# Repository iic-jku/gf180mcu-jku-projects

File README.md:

# wafer.space gf180mcuD MPW Multi-Project Chip

(c) 2025-2026 Simon Dorrer (JKU), Jonathan Hager (JMU), Dominik Brandstetter (JKU) and [co-designers](https://github.com/iic-jku/gf180mcu-jku-projects/blob/main/AUTHORS.md).

Project `JKU1` for wafer.space MPW run using the `gf180mcuD` PDK.

<p align="center">
  
  <br>
  <em>Chip-on-Board (CoB) wire-bonded die of the wafer.space gf180mcuD chip.</em>
</p>

<p align="center">
  
  <br>
  <em>Micrograph of CoB wire-bonded die of the wafer.space gf180mcuD chip with ruler on the right side.</em>
</p>

<p align="center">
  
  &nbsp;
  
  <br>
  <em>Micrograph of the bare die (left) and render of the layout (right) of the wafer.space gf180mcuD chip (4mm x 5mm).</em>
</p>

## Sanity Bring-Up Test

We wired up the DIP adapter PCB on a breadboard. We supplied the board with 3V3 or 5V via decoupling capacitors, connected an AWG to the clock input, and tied the reset input to high: the sanity bring-up test works. On one digital output, the Super Mario Bros. theme song is played via a buzzer through a PWM signal. Nothing fancy, just a quick breadboard build-up and test, but at least we can say that the chip is alive!

https://github.com/user-attachments/assets/dcc359f1-c54c-4383-b16b-32720ad51963
<p align="center">
  <em>Sanity bring-up test playing the Super Mario Bros. theme song.</em>
</p>

## Overview

- [x] **GDS Submission:** https://platform.wafer.space/
- [x] **Precheck:** https://github.com/wafer-space/gf180mcu-precheck
- [x] **Projects (Pass):**
  - [x] Multiplexer (Simon Dorrer - JKU)
    - **N/A Reg to Reg Paths**
  - [x] TinyWhisper RISC-V (Jonathan Hager - JMU)
    - **setup violation for SS corner**
  - [x] TinyTone (Jakob Schaumberger - JKU)
  - [x] Decimation Filter (Michael Köfinger - JKU)
    - **N/A Reg to Reg Paths**
  - [x] Octowave (Max Golser - JKU)
    - **setup violation for SS corner**
  - [x] Tetris (Dominik Brandstetter - JKU & HTL Leonding)
    - **setup violation for SS corner**
  - [x] TinyStack (Linzer Technikum)
  - [x] TinyBF (Rene Hahn - JKU)
  - [x] SAR ADC Controller (Ilir Shala - JKU)
  - [x] LED Spinner (Tim Tremetsberger - JKU)
    - **N/A Reg to Reg Paths**
  - [x] TinyToneGen (Felix Feierabend - JKU)
    - **N/A Reg to Reg Paths**
  - [x] Digital Filter (Gregor Flachs - JKU)
  - [x] Traffic Light Controller (Maximilian Kernmaier - JKU)
  - [x] VGA Clock (Timo Laimer - JKU)
    - **setup violation for SS corner**

## Prerequisites

We use a custom fork of the [gf180mcuD PDK variant](https://github.com/wafer-space/gf180mcu) until all changes have been upstreamed.

To clone the latest PDK version, simply run `make clone-pdk`.

In the next step, use LibreLane within the IIC-OSIC-TOOLS container with tag `2026.04` or later or install LibreLane by following the Nix-based installation instructions: https://librelane.readthedocs.io/en/latest/installation/nix_installation/index.html

## Implement the Design

This repository contains a Nix flake that provides a shell with the [`leo/gf180mcu`](https://github.com/librelane/librelane/tree/leo/gf180mcu) branch of LibreLane.

Simply run `nix-shell` in the root of this repository.

> [!NOTE]
> Since we are working on a branch of LibreLane, OpenROAD needs to be compiled locally. This will be done automatically by Nix, and the binary will be cached locally. 

With this shell enabled, run the implementation:

```
make librelane
```

This command is also available for the macros.

## View the Design

After completion, you can view the design using the OpenROAD GUI:

```
make librelane-openroad
```

Or using KLayout:

```
make librelane-klayout
```

These commands are also available for the macros.

## Copying important Reports to the Reports Folder

To copy yosys, antenna violations, hold & setup timing and manufacturability reports of the latest run to the `reports/` folder in the root directory of the repository, run the following command:

```
make copy-reports
```

This will only work if the last run was completed without errors. This command is also available for the macros.

## Copying the Design to the Final Folder

To copy your latest run to the `final/` folder in the root directory of the repository, run the following command:

```
make copy-final
```

This will only work if the last run was completed without errors. This command is also available for the macros.

## Copying the final GDS to the GDS Folder

To copy and ZIP your latest GDS in the `final/` folder in the root directory of the repository and save it in the `gds/` folder, run the following command:

```
make copy-gds
```

This will only work if the last run was completed without errors.

## Render Layout of the Design

To render your latest GDS in the `final/` folder in the root directory of the repository and save it in the `img/` folder, run the following command:

```
make render-image
```

This will only work if the last run was completed without errors. This command is also available for the macros.

## Build Macros

To build a specific macro, look into the `Makefile` and run the corresponding command. For example, the following command builds the `tetris` macro:

```
make build-tetris
```

To build all macros, run the following command:

```
make build-all-macros
```

For each macro the following commands are executed: `make librelane`, `make copy-reports`, `make copy-final` and `make render-image`.

## Build All

To clone the PDK, build all macros, build the top-level chip, copy its reports, copy its `final/` folder, copy and ZIP its GDS, render its GDS and display it in the OpenROAD GUI, run the following command:

```
make build-all
```

This is especially useful for people who want to rebuild our chip from scratch. Just clone this repo, run `nix-shell` in the root of this repository and run `make build-all`. Enjoy. :-)

## Verification and Simulation

We use [cocotb](https://www.cocotb.org/), a Python-based testbench environment, for the verification of the chip.
The underlying simulator is Icarus Verilog (https://github.com/steveicarus/iverilog).

The testbench is located in `cocotb/chip_top_tb.py`. To run the RTL simulation, run the following command:

```
make sim
```

To run the GL (gate-level) simulation, run the following command:

```
make sim-gl
```

> [!NOTE]
> You need to have the latest implementation of your design in the `final/` folder. After implementing the design, execute 'make copy-final' to copy all necessary files.

In both cases, a waveform file will be generated under `cocotb/sim_build/chip_top.fst`.
You can view it using a waveform viewer, for example, [GTKWave](https://gtkwave.github.io/gtkwave/).

```
make sim-view
```

You can now update the testbench according to your design.

## Cite This Work

```
@software{2025_WS_MPW,
	author = {Dorrer, Simon and Hager, Jonathan},
	month = dec,
	year = {2025},
	title = {{GitHub Repository for a wafer.space MPW Multi-Project Chip}},
	url = {https://github.com/iic-jku/gf180mcu-jku-projects},
	doi = {10.5281/zenodo.19654471}
}
```

## Acknowledgements

This project is supported by [wafer.space](https://wafer.space/) and the [Johannes Kepler University](https://jku.at).

<table width="100%">
  <tr>
    <td align="left" width="50%">
      
    </td>
    <td align="right" width="50%">
      
    </td>
  </tr>
</table>

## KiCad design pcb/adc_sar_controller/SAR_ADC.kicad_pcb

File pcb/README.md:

# PCB Notes

## Authors

- Simon Dorrer
- Dominik Brandstetter
- Jakob Schaumberger
- Max Zaglmayr
- Max Golser
- Rene Hahn

## TODO

- Order DIP breakout boards: Simon Dorrer

## Links

- CoB breakout board: https://github.com/wafer-space/chip-on-board-wire-bonded-pcbs
- Tiny Tapeout demo PCB: https://github.com/TinyTapeout/tt-demo-pcb
- Tiny Tapeout PCB files: https://github.com/TinyTapeout/pcb-files
- Tiny Tapeout GF 0p2 mezzanine adapter PCB: https://github.com/htfab/breakout-ttgf0p2-ws-adapter
- VGA breakout board: https://github.com/mole99/tiny-vga
- GF180MCU-D JKU projects: https://github.com/iic-jku/gf180mcu-jku-projects

## Required Components

### General

- 1x 3-bit DIP switch
- 3x buttons + reset
- Copy the Tiny Tapeout VGA breakout board
- External GPIO headers (see Tiny Tapeout demo PCB)
- Fan for cooling (optional)

### MCU

- See Tiny Tapeout demo PCB
- Connect all inputs to the MCU
- Connect all outputs to the MCU
- USB-C
- I2C display
- Pin count TBD: PCA9555 IO/I2C or RP2350
- Level shifter (3.3 V / 5 V)

### Octowave

- Multiple-feedback filters (Max Golser)

### TinyWhisper

- See TinyWhisper PCB (Simon Dorrer)

### Decimation Filter

- SPI

### TinyTone

- Switching transistor + buzzer

### Tetris

- SNES connector to MCU (copy from Tiny Tapeout demo PCB)
- VGA output (see Tiny Tapeout demo PCB)
- Dominik Brandstetter + HTL Leonding

### TinyStack

- 8x LEDs

### TinyBF

- Input + Outputs to MCU
- UART + Testpads

### SAR ADC Controller

- Do not connect `comp_in` with MCU
- Connect 8-Bit DAC traces with MCU and DAC (switchable)
- Analog Front-End (maybe provided by Ilir)
	- DAC
	- Comparator
	- S&H

### LED Spinner

- 7-segment display (see Tiny Tapeout boards)
- Buttons

### TinyToneGen

- Low-pass active filter

### Digital Filter

- MCU only

### Traffic Light Control

- LED matrix for pedestrian signs
- LEDs for traffic lights
- Silkscreen for pedestrian crossing

### VGA Clock

- Combine VGA with Tetris (OR)

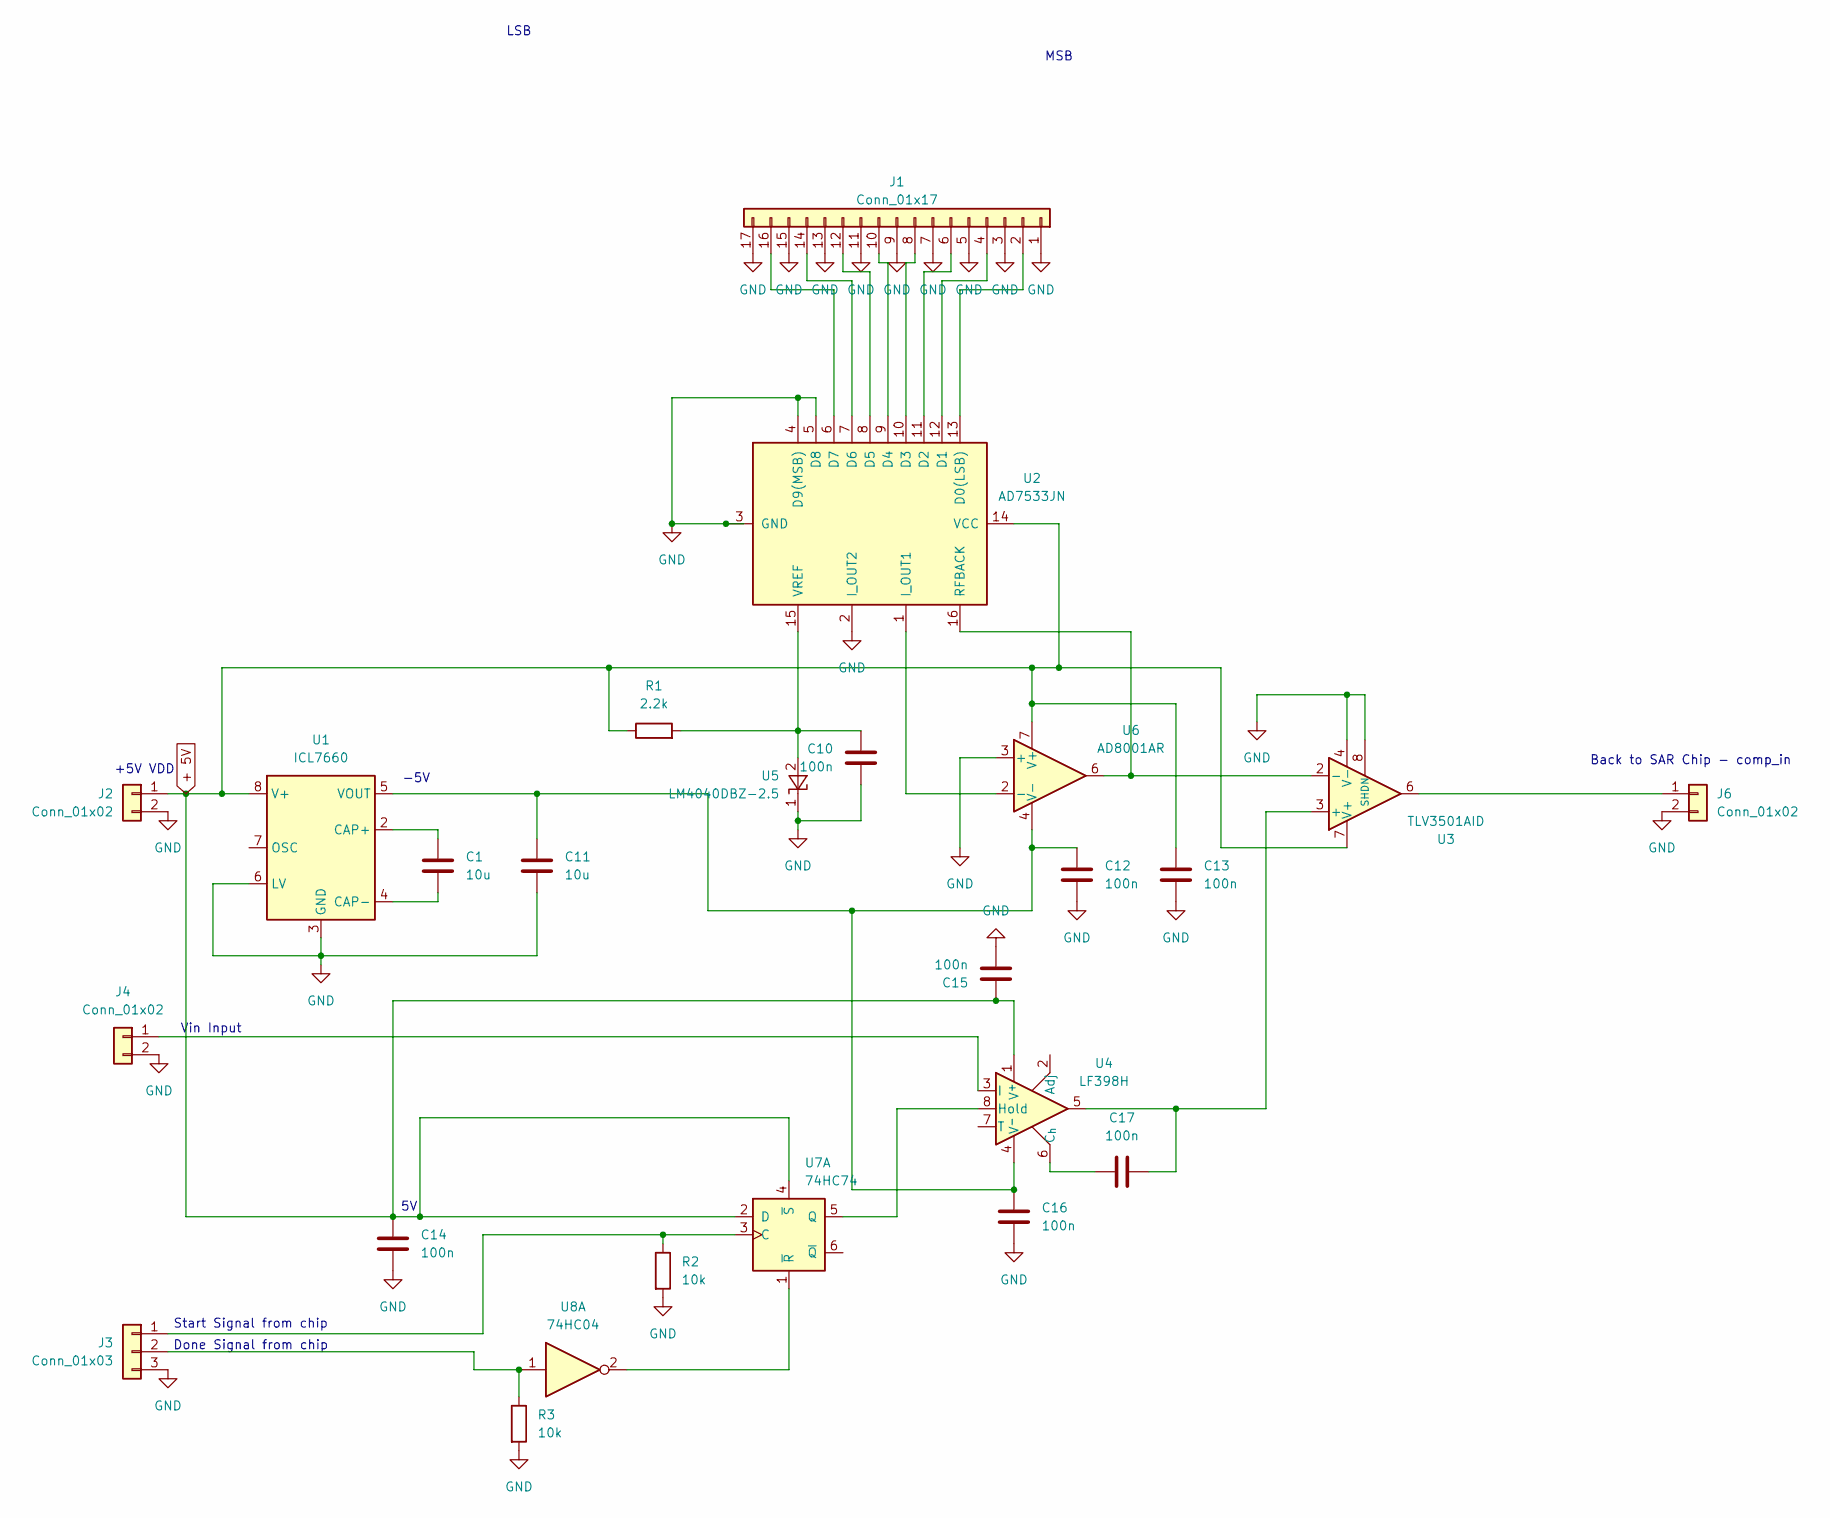
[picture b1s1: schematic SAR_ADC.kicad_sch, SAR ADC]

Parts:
C1, C11: 10u; C_1206_3216Metric
C10, C12, C13, C14, C15, C16, C17: 100n; C_0805_2012Metric
J1: Conn_01x17; PinHeader_1x17_P2.54mm_Vertical
J2, J4, J6: Conn_01x02; PinHeader_1x02_P2.54mm_Vertical
J3: Conn_01x03; PinHeader_1x03_P2.54mm_Vertical
R1: 2.2k; R_0805_2012Metric
R2, R3: 10k; R_0805_2012Metric
U1: ICL7660; DIP-8_W7.62mm_Socket
U2: AD7533JN; DIP-16_W7.62mm_Socket
U3: TLV3501AID; SOIC-8_3.9x4.9mm_P1.27mm
U4: LF398H; TO-99-8
U5: LM4040DBZ-2.5; SOT-23
U6: AD8001AR; SOIC-8_3.9x4.9mm_P1.27mm
U7: 74HC74; DIP-14_W7.62mm_Socket
U8: 74HC04; DIP-14_W7.62mm_Socket

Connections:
+ 5V: C13.1, C14.1, C15.1, J2.1, R1.1, U1.8 (V+), U2.14 (VCC), U3.7 (V+), U4.1 (V^{+}), U6.7 (V+), U7.2 (D), U7.4 (~S)
GND: C10.2, C11.2, C12.2, C13.2, C14.2, C15.2, C16.2, J1.1, J1.3, J1.5, J1.7, J1.9, J1.11, J1.13, J1.15, J1.17, J2.2, J3.3, J4.2, J6.2, R2.2, R3.2, U1.3 (GND), U1.6 (LV), U2.2 (I_OUT2), U2.3 (GND), U2.4 (D9(MSB)), U2.5 (D8), U3.4 (V-), U3.8 (SHDN), U5.1 (K), U6.3 (+)
unnamed: J1.2, U2.13 (D0(LSB))
unnamed: J1.4, U2.12 (D1)
unnamed: J1.6, U2.11 (D2)
unnamed: J1.8, U2.10 (D3)
unnamed: J1.10, U2.9 (D4)
unnamed: J1.12, U2.8 (D5)
unnamed: J1.14, U2.7 (D6)
unnamed: J1.16, U2.6 (D7)
unnamed: J3.1, R2.1, U7.3 (C)
unnamed: J3.2, R3.1, U8.1
unnamed: J4.1, U4.3 (I)
unnamed: J6.1, U3.6
unnamed: C1.1, U1.2 (CAP+)
unnamed: C1.2, U1.4 (CAP-)
unnamed: C11.1, C12.1, C16.1, U1.5 (VOUT), U4.4 (V^{-}), U6.4 (V-)
unnamed: U2.1 (I_OUT1), U6.2 (-)
unnamed: U2.16 (RFBACK), U3.2 (-), U6.6
unnamed: C10.1, R1.2, U2.15 (VREF), U5.2 (A)
unnamed: C17.2, U3.3 (+), U4.5
unnamed: C17.1, U4.6 (C_{h})
unnamed: U4.8 (Hold), U7.5 (Q)
unnamed: U7.1 (~R), U8.2

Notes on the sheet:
Back to SAR Chip - comp_in
Done Signal from chip
+5V VDD
MSB
-5V
Vin Input
LSB
Start Signal from chip

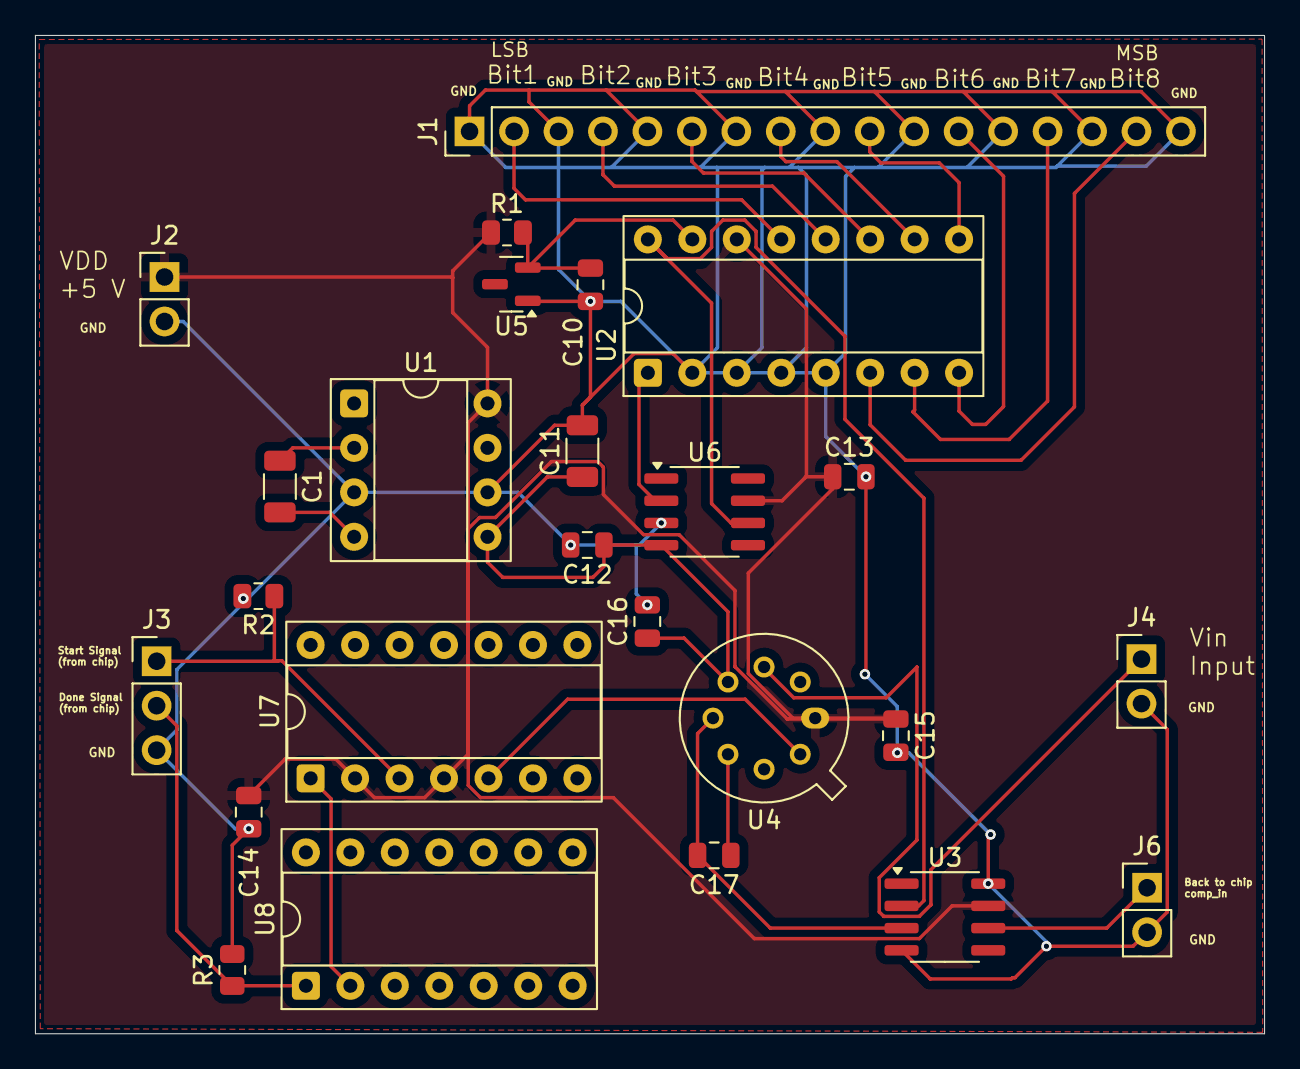
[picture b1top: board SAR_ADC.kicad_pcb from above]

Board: 2 copper layers, 70.2 x 57.0 mm, 25 parts (0 on the bottom side), 24 nets.

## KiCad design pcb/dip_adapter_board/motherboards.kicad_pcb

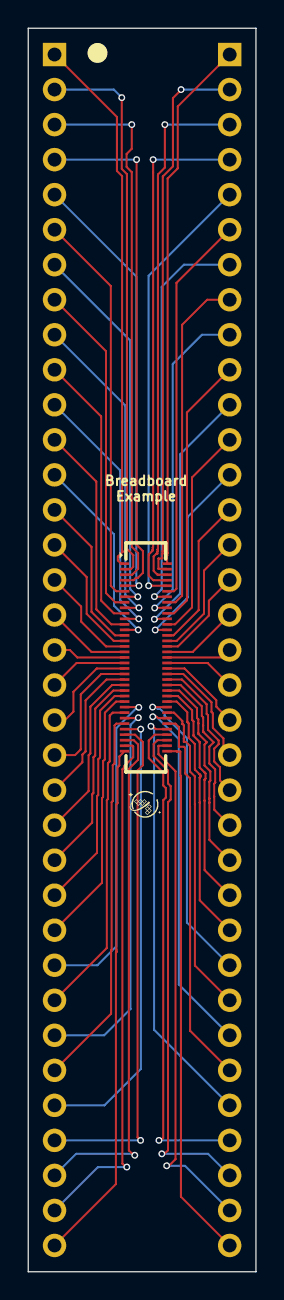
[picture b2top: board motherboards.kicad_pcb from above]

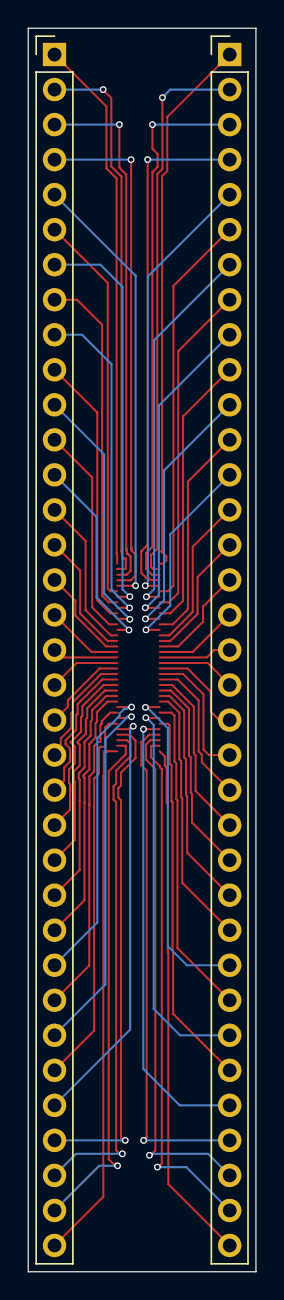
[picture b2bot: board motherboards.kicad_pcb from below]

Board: 2 copper layers, 16.5 x 90.2 mm, 3 parts (2 on the bottom side), 70 nets.

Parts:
J101, J103: DS1021-1x35SF11-B; PinHeader_1x35_P2.54mm_Vertical
J102: HC-PBB40C-70DS-0.4V-2.0-02; CONN-SMD_70P-P0.40_HC-PBB40C-70DS-0.4V-3.0-02

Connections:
unnamed: J101.1, J102.1
unnamed: J101.2, J102.2
unnamed: J101.3, J102.3
unnamed: J101.4, J102.4
unnamed: J101.5, J102.5
unnamed: J101.6, J102.6
unnamed: J101.7, J102.7
unnamed: J101.8, J102.8
unnamed: J101.9, J102.9
unnamed: J101.10, J102.10
unnamed: J101.11, J102.11
unnamed: J101.12, J102.12
unnamed: J101.13, J102.13
unnamed: J101.14, J102.14
unnamed: J101.15, J102.15
unnamed: J101.16, J102.16
unnamed: J101.17, J102.17
unnamed: J101.18, J102.18
unnamed: J101.19, J102.19
unnamed: J101.20, J102.20
unnamed: J101.21, J102.21
unnamed: J101.22, J102.22
unnamed: J101.23, J102.23
unnamed: J101.24, J102.24
unnamed: J101.25, J102.25
unnamed: J101.26, J102.26
unnamed: J101.27, J102.27
unnamed: J101.28, J102.28
unnamed: J101.29, J102.29
unnamed: J101.30, J102.30
unnamed: J101.31, J102.31
unnamed: J101.32, J102.32
unnamed: J101.33, J102.33
unnamed: J101.34, J102.34
unnamed: J101.35, J102.35
unnamed: J102.36, J103.35
unnamed: J102.37, J103.34
unnamed: J102.38, J103.33
unnamed: J102.39, J103.32
unnamed: J102.40, J103.31
unnamed: J102.41, J103.30
unnamed: J102.42, J103.29
unnamed: J102.43, J103.28
unnamed: J102.44, J103.27
unnamed: J102.45, J103.26
unnamed: J102.46, J103.25
unnamed: J102.47, J103.24
unnamed: J102.48, J103.23
unnamed: J102.49, J103.22
unnamed: J102.50, J103.21
unnamed: J102.51, J103.20
unnamed: J102.52, J103.19
unnamed: J102.53, J103.18
unnamed: J102.54, J103.17
unnamed: J102.55, J103.16
unnamed: J102.56, J103.15
unnamed: J102.57, J103.14
unnamed: J102.58, J103.13
unnamed: J102.59, J103.12
unnamed: J102.60, J103.11
unnamed: J102.61, J103.10
unnamed: J102.62, J103.9
unnamed: J102.63, J103.8
unnamed: J102.64, J103.7
unnamed: J102.65, J103.6
unnamed: J102.66, J103.5
unnamed: J102.67, J103.4
unnamed: J102.68, J103.3
unnamed: J102.69, J103.2
unnamed: J102.70, J103.1

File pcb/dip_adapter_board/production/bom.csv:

Designator,Footprint,Quantity,Value,LCSC Part #
"J101, J103",PinHeader_1x35_P2.54mm_Vertical,2,DS1021-1x35SF11-B,C7430391
J102,CONN-SMD_70P-P0.40_HC-PBB40C-70DS-0.4V-3.0-02,1,HC-PBB40C-70DS-0.4V-2.0-02,C19089262

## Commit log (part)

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2025-11-26 added .gitattributes
2025-11-26 started planning projects
2025-11-27 updated pin_planning.txt and projects.txt
2025-11-27 added macro LEDSpinner
2025-11-27 added macro digital_filter
2025-11-27 added macro traffic_light_controller
2025-11-27 renamed LEDSpinner to led_spinner (naming convention)
2025-11-27 added macro tiny_bf
2025-11-27 added macro classic_vga_clock
2025-11-28 added testbench for led_spinner
2025-11-28 updated traffic_light_controller Verilog files
2025-11-28 added macro tiny_tonegen
2025-11-28 removed unnecessary files in tiny_tonegen verilog/src
2025-11-28 added _out to output signals in classic_vga_clock design
2025-11-28 [FP, Timing] Floorplanning for student projects, checked all timing reports
2025-11-28 added macro adc_sar_controller
2025-11-28 updated student floorplan with SAR ADC Controller
2025-11-28 updated verilog files for classic_vga_clock
2025-11-28 added timing summary for classic_vga_clock
2025-11-28 added macro decimation_filter_256_ser
2025-11-28 updated config.yaml for decimation_filter_256_ser
2025-11-28 added OpenROAD GUI layout pictures (.PNG)
2025-11-28 added macro octawave
2025-11-28 added OpenROAD GUI layout picture (.PNG) for decimation_filter_256_ser
2025-11-28 [Server] Ran LibreLane flow for decimation filter
2025-11-28 Add TinyWhisper Verilog sources
2025-11-28 Add TinyWhisper librelane configs
2025-11-28 Remove verilator linter commands
2025-11-28 Add tinywhisper to documentation txts
2025-11-28 Add testbench for tinywhisper
2025-11-28 updated tinywhisper_riscv macro for librelane flow
2025-11-28 added SYNTH_STRATEGY comments to all config.yaml files
2025-11-29 added OpenROAD GUI layout picture (.PNG) for tinywhisper_riscv
2025-11-29 updated Verilog files for tiny_bf
2025-11-29 re-ran librelane for tiny_bf
2025-11-29 added OpenROAD GUI layout picture (.PNG) for octawave
2025-11-29 [Server] Timing Reports for octawave & tinywhisper_riscv
2025-11-29 updated projects.txt --> ready for top-level assembly
2025-11-29 updated OpenROAD GUI layout picture (.PNG) for tinywhisper_riscv
2025-11-29 [Server] finalized tinywhisper_riscv
2025-11-29 added macro tiny_tone
2025-11-29 added macro multiplexer
2025-11-29 updated floorplan
2025-11-29 added simple testbench for multiplexer
2025-11-29 updated projects and floorplan
2025-11-29 updated top-level config.yaml (hotfix from Leo)
2025-11-29 updated Pin planning
2025-11-30 added macro tetris
2025-11-30 updated floor and pin planning
2025-11-30 finished floorplan
2025-11-30 updated SAR ADC Controller
2025-11-30 added OpenROAD GUI layout picture (.PNG) for tetris
2025-11-30 [Server] Finished LibreLane Flow for Tetris
2025-11-30 added floorplan_pinplan_drawing.pdf
2025-12-01 updated floorplan_pinplan_drawing.pdf
2025-12-01 Update tinywhisper_riscv with the final state
2025-12-01 updated pin_order.cfg for all macros according to floorplan / pinplan
2025-12-01 added IICQC logo
2025-12-01 updated multiplexer --> finalization of macros --> run them all on Server
2025-12-01 updated octowave macro
2025-12-01 renamed octawave to octowave
2025-12-01 updated slot_defines.svh with correct IOs
    // Power/ground pads for core and I/O
    `define NUM_DVDD_PADS 2
    `define NUM_DVSS_PADS 2
    // Signal pads
    `define NUM_INPUT_PADS 29
    `define NUM_BIDIR_PADS 41
2025-12-01 updated slot_defines.svh with correct IOs
2025-12-01 updated floorplan_pinplan_drawing.pdf for reference PCB VSS / VDD (only four pins)
2025-12-01 updated chip_core.sv with clock A to D, added TinyTone
2025-12-01 added VSS / VDD pins to macro top-level interfaces
2025-12-01 removed analog pins in chip_core.sv
2025-12-01 added CoB pinout --> redesign of pinplan ;-(
2025-12-01 updated pin_planning.txt and slot_defines.svh for new pinplan
2025-12-01 updated top-level verilog for first test
2025-12-01 added CoB_example.png
2025-12-01 updated files for sanity test
2025-12-01 fixed typo in slot_1x1.yaml
2025-12-01 fixed errors in top-level verilog
2025-12-01 fixed error in config.yaml
2025-12-01 updated config.yaml with tiny_tone.v reference
2025-12-01 added tiny_tone.v include to chip_core.sv
2025-12-01 did chip_core.sv and chip_top.sv again
2025-12-01 fixed chip_top.sv
2025-12-01 fixed pin order for multiplexer
2025-12-02 updated pin_planning
2025-12-02 fixed instance path error in config.yaml
2025-12-02 updated pin_order.cfg for all macros for new floorplan
2025-12-02 TinyWhisper: Add SPI slow mode and Power pins
2025-12-02 [Server] updated config.yaml for all macros
2025-12-02 Add Makefiles for nix-shell flow
2025-12-02 added macros as comments
2025-12-02 updated projects.txt (final area per macro)
2025-12-02 finalized (hopefully) floorplan
2025-12-02 updated slot_1x1.yaml with correct pinout
2025-12-02 updated config.yaml (placed tiny_tone according to floorplan)
2025-12-02 added decimator, octowave and tiny_tone to top-level, added locations for all other macros
2025-12-02 Add gds and library files for jku and jmu logos
2025-12-02 updated config.yaml
    higher CLOCK_PERIOD: Top-level timing analysis is irrelevant for setup times, as the individual projects each have their own clock period.
2025-12-02 updated chip_top.sv with JKU / JMU CE logos
2025-12-02 Add spi_slow_mode pin back to TinyWhisper
2025-12-02 finished top-level config.yaml and chip_core.sv
    Fingers crossed!
2025-12-02 fixed path error in config.yaml
2025-12-02 updated config.yaml (hardcoded CORE_AREA[0] due to problems with openroad GUI)
2025-12-02 fixed error in chip_core.sv
2025-12-02 updated config.yaml (hardcoded CORE_AREA[0] due to problems with openroa…
2025-12-02 updated classic_vga_clock macro
2025-12-02 Add Makefiles for all macros
2025-12-03 Add cocotb tests for TinyWhisper
2025-12-03 Edit Verilog sources to work with cocotb runner()
2025-12-03 added chip_top_layout.png
2025-12-03 Update JKU logo
2025-12-03 Add missing pnl verilog models to cocotb
2025-12-03 Add tests for all multiplexer modules
2025-12-03 Add first drc clean gds submission without lib
2025-12-04 Add buffer to rst_n_PAD
2025-12-05 Update project to new PDK template
2025-12-05 Update project and macros with new template
2025-12-09 updated Verilog files of tiny_tonegen macro
2025-12-09 TinyWhisper: Add dsmod configurations per MMIO
2025-12-09 updated simulate.sh in tiny_tonegen macro
2025-12-09 increased area for tiny_tonegen, updated floorplan
2025-12-09 updated floorplan (give more area to octowave, tetris and TinyWhisper CPU)
    -) give more area to octowave, tetris and TinyWhisper CPU
    -) swapped location of tetris and TinyWhisper CPU due to hold violations on pin SO
2025-12-09 updated repo to new version
2025-12-09 updated macro Makefiles with new template
2025-12-10 changed gf180mcu_dev to gf180mcu PDK
2025-12-10 TinyWhisper: Fix dsmod invert
2025-12-10 Add hold buffers and disable setup violations
2025-12-10 finalized macro tiny_tonegen
2025-12-10 added macro tiny_stack (LiTec)
2025-12-10 integrated tiny_stack to top-level
2025-12-10 updated top-level Makefile with tiny_stack
2025-12-10 added report and layout PNG placeholder for tiny_stack
2025-12-10 TinyWhisper: fix copy-paste error for sin_ds
2025-12-11 updated final path for all macros in config.yaml
2025-12-11 [Server] regenerated logos
2025-12-11 [Server] added img and docs folder
2025-12-11 added chip_top_layout_gui.png
2025-12-11 renamed gds_submissions to gds
2025-12-11 changed location of CoB_package
2025-12-11 added placeholder folder for reports
2025-12-11 relocated layout images and reports per macro
2025-12-12 added some comments in tiny_stack.v
2025-12-12 Fix tiny_tonegen imports
2025-12-12 Fix TinyWhisper gpio typo
2025-12-12 Integrate tiny_stack into cocotb
2025-12-12 Fix antenna violations with ECO Step
2025-12-13 added comments to config files
2025-12-13 updated AUTHORS.md
2025-12-13 added email to AUTHORS.md
2025-12-13 added comments
2025-12-13 updated SAR ADC makefile and top-level makefile
    -) added make copy-reports & make render-image
2025-12-13 fixed Makefile
2025-12-13 updated Makefiles for all macros
2025-12-13 updated top-level Makefile
    -) make copy-reports
    -) make build-all
    -) added copy-reports and render-image to all macros
2025-12-14 Add max slew and cap parameters
2025-12-14 Add proper reset logic to tiny_tonegen
2025-12-14 Add stimuli to tiny_tonegen cocotb testbench
2025-12-14 resimulate tiny_tonegen
2025-12-14 Fix Tiny_tonegen by adding rst to sensitivity
2025-12-14 updated PDK to 1.6.5., added magic DRC update to config (out-commented)
2025-12-14 updated floorplan for bigger tiny_tonegen
2025-12-14 added * wildcard to ignore step numbers in Makefiles
2025-12-14 updated Makefiles again
2025-12-14 updated Makefiles (wrong PHONY: render-image)
2025-12-14 updated ReadMe with new commands
2025-12-14 finalized README.md
2025-12-15 added copy-gds to Makefile
2025-12-15 added copy-gds to ReadMe
2025-12-15 added copy-gds to build-all in Makefile
2025-12-15 [Server] push all build files
2025-12-15 updated chip_top_layout_gui.png
2025-12-15 added ZIP to copy-gds
2025-12-15 finalized README.md / submitted GDS
2025-12-15 added final submission GDS
2025-12-15 added cocotb results
2025-12-15 finalized README.md
    -) added chip_top_white.png
2025-12-15 finalized README.md
    -) added chip_top_layout_gui.png
2025-12-15 fixed copy-gds target in Makefile
2025-12-16 updated to PDK 1.6.6
2025-12-17 updated copy-gds in Makefile
2026-04-14 added README.md with first plans to pcb folder
2026-04-15 updated pcb/README.md
2026-04-18 updated README.md, added CITATION.cff
2026-04-19 added DOI
2026-04-19 deleted .github folder
2026-04-19 updated Makefile (target copy-gds)
2026-04-19 added chip_top.gds.gz (instead of .zip)
2026-04-19 added `release` folder with tapeout .gds.gz
2026-04-20 added Copyright headers
2026-04-23 added die_foto
2026-04-28 added dip_adapter_board folder
2026-04-28 added images to release folder, updated README
2026-04-28 cropped images
2026-05-08 added pcb/adc_sar_controller files
2026-05-10 added breadboard testing images & video
2026-05-10 added Acknowledgements
2026-05-10 updated README.md (added sanity bring-up test)
2026-05-13 updated .gitignore
2026-05-13 added further images from Keyence microscope
2026-05-13 added more images
2026-05-16 upgraded from "Apache-2.0" to "Apache-2.0 WITH SHL-2.1" license
2026-05-23 added `resin_cubes.jpg`
2026-05-28 added new floorplan drawing and pinout for motherboard adapter
